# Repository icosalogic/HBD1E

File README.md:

# HBD1E
Kicad project for a configurable gate driver board to drive two MOSFETs with TO-247-4 package and
pinout [Drain, Source, KelvinSource, Gate].

Front side of board:

Back side of board:

# Features

- Supports 2 independent channels with 1 MOSFET per channel.
- No high-power connections on the board.  The user is free to connect the MOSFET power pins in any configuration they wish.
- Utilizes a gate driver chip in an SOIC-16 wide package, with a pin layout supported by multiple vendors.
- Each channel can be independently configured to be isolated from the gate driver control circuit.
- Each channel can be independently configured to use a linear regulator to precisely control the gate driver voltage.
- Most compatible gate driver chips support configurable dead time.

# Applications

- Half bridge, with input and output having a common ground: Configure the high side to be isolated, and the
low side non-isolated.
- T-Type inverter leg: Use 2 boards, with all gate power domains isolated, with the two middle MOSFETs configured
appropriately for common drain or common source.
- High power parallel MOSFETs: Disable dead time on the gate driver chip, and configure both MOSFET power
domains as non-isolated.

# Board Connections

Board input pins:  

- PWMH: PWM signal for the high-side MOSFET Q1, uses typical CMOS switching levels (off <= 0.8V, on >= 2.0V).
- PWML: PWM signal for the low-side MOSFET Q2, uses typical CMOS switching levels.
- DISABL: Pull this value low to enable the driver chip.  There is a pull up resistor to VCC on this circuit,
so the control component must pull this signal low to enable switching.  Uses typical CMOS switching levels.
- GND: Ground common to VCC and VGD.
- VCC: Power to the control side of the gate driver chip.  Typically 3.3V or 5V, maximum 20V.
- VGD: Power to the gate driver regions, optionally through isolation modules.

For the reference gate driver chip UCC21520, VCC and VGD may be the same for applications with lower
gate voltages.  Or you may choose to have them be separate, and use a higher voltage VGD to gain headroom
through the isolated modules, and configure the linear regulators to provide a precise post-isolation
gate drive voltage.

Note that there are no on-board connections for the high-current drain and source pins for either
MOSFET Q1 or Q2.  These must be connected separately, either through appropriately-sized wires or
a properly-designed laminated bus.

# Schematic

# PCB Layout Details

PCB components:

Front copper layer:

Back copper layer:

# Configuring Channel Isolation

The front of the board has marked locations for two DC-DC isolated modules, U3 (high side, shown below) and U5 (low side).

These modules take power from the VGD pin, and supply it to the regions of the PCB driving the gates for
the high side MOSFET Q1 and the low side MOSFET Q2.

To make either region isolated, solder a DC-DC isolated converter module in the marked location.
Our test boards used a Gaptec 3S7B-2424S3UP, but pin-compatible 7-SIP components are available from multiple manufacturers.

To make one of these power domains non-isolated, solder a wire connection from + to + and another from - to -.
Ordinary AWG 20 gauge hookup wire is adequate.

# Configuring Gate Drive Voltage Regulation

On the back side of the board, under the isolated modules U3 and U5, are locations for LM317 linear regulators
and associated components.

- High Side: (under U3) U4, D3, D4, C10, C11, R14, R15, R16
- Low Side: (under U5) U2, D1, D2, C7, C9, R11, R12, R13

The following table shows which resistors on this board map to those in a typical LM317 datasheet.
This should allow you to select resistor values to configure your desired gate driver voltage.

| Datasheet | High Side | Low Side |
| --------- | --------- | -------- |
|    R1     |    R16    |   R11    |
|    R2     |  R14+R15  | R12+R13  |

Note that we used 2 resistors in series for the R2 resistor from the datasheet.
The power dissipation from the minimum regulation current may exceed the limit for a typical
1/10 watt resistor, so we use 2 resistors in series to spread the thermal load.

Here is a table showing combinations for some typical gate drive voltages, using common resistor values.
Of course, more precise voltages can be obtained using more specific resistor values and higher
tolerance 0.1% resistors.

| Target Voltage | R16/R11 | R14+R15/R12+R13 | Computed Voltage |
| -------------- | ------- | --------------- | ---------------- |
|       10       |   180   |     270/1000    |      10.069      |
|       12       |   180   |     560/1000    |      12.083      |
|       15       |   180   |    1000/1000    |      15.139      |
|       18       |   180   |    1200/1200    |      17.917      |
|       20       |   180   |    1200/1500    |      20.000      |

Note also that the LM317 is a very robust device that may not require all the configured components.
The adjust capacitors may be omitted if your testing shows that ripple and other voltage transients
do not cause any downstream issues when switching the MOSFETs.
Each of the adjust capacitors is paired with a diode:

- C9, D2
- C11, D4

If you omit the adjust capacitor, you can also omit the matching diode.  If you use the adjust capacitor,
you should also use the diode to prevent the capacitor from discharging through the regulator in a power off
scenario.

Also note that you should always populate D1 and D3, since there are large capacitors for the gate driver
chip that may discharge through the regulator in a power off scenario.  D1 and D3 will prevent this.

To configure either the high-side or low-side power domain for voltage regulation, populate the associated
components as listed above.

To configure either of the power domains without voltage regulation, omit all of the regulation components
listed above for that domain, and replace the associated diode (D1 or D3) with a 0 ohm shunt resistor.

# Configuring Dead Time

The components used to configure dead time are R1, R10 and C6.

Some, but not all of the pin-compatible gate driver chips support controlling dead time between Q1 and Q2
gate transitions, using a resistor connected to pin 6.  If the gate driver chip you use does not support dead
time generation, then do not populate R1, R10 and C6, and ignore the rest of this section.

If your gate driver chip supports dead time insertion, populate R10 and optionally C6 according to the
datasheet for your chip.  Do not populate R1.

If your chip supports dead time insertion, but you wish to suppress it, populate R1, but not R10 and C6.
This may be desireable if you use this board in a high-current parallel MOSFET application, where you want
both MOSFETs on at the same time.

If your control logic providing the PWM signals also implements dead time, one strategy is to program an
absolute minimum dead time via the hardware as described in this section, and program an optimized, longer
dead time in your control logic.  The gate driver chip uses the longer of the hardware configured dead
time or the software-controlled dead time in the PWM inputs.

# Configuring Input Signal Filtering

Each of the 3 input signals from the controller to this gate driver board has an RC circuit to
filter transients that may cause issues for the gate driver IC input logic.  These signals and the
associated filter components are listed below.

| Signal Name | Filter Resistor | Value | Capacitor | Value | Pull Up Resistor | Value |
| ----------- | --------------- | ----- | --------- | ----- | ---------------- | ----- |
|     PWMH    |       R4        |  47Ω   |     C1    |  33pF |                  |       |
|     PWML    |       R5        |  47Ω   |     C4    |  33pF |                  |       |
|    DISABL   |       R6        |  47Ω   |     C5    |   1nF |        R7        |  10k  |

The size of all these components is 0805, making them less trouble to hand solder while changing
filter components.

# Test Points

There are numerous test points located on both sides of the board to which users can solder
surface mount test point loops, for example KOA Speer RCWCTE.
This gives you the ability to clip oscilloscope leads to enable monitoring various signals while
debugging the gate driver configuration.

### Caution!  This board may use high voltages that are hazardous to humans.
- Be very careful when connecting test leads to potentially high voltage points on the circuit board.
- High voltages may also break test equipment if proper grounding and isolation practices are not followed.
- Please be careful!

List of test points on the board:
| Label |  Name    | Location | Description                                     |
| ----- | ------   | -------- | ----------------------------------------------- |
| TP1   | HS Gate  | Bottom   | High side MOSFET gate pin                       |
| TP2   | LS Gate  | Bottom   | Low side MOSFET gate pin                        |
| TP3   | VDDB     | Bottom   | Low side post-regulated gate driver voltage     |
| TP4   | VDDA     | Top      | High side post-regulated gate driver voltage    |
| TP5   | VDDA_ISO | Bottom   | High side post-isolation, pre-regulated voltage |
| TP6   | PWMHF    | Top      | High side post-filter PWM input signal          |
| TP7   | PWMLF    | Top      | Low side post-filter PWM input signal           |
| TP8   | DISF     | Top      | Disable post-filter input signal                |
| TP9   | VCC      | Top      | Logic side power for gate driver chip           |
| TP10  | VGD      | Bottom   | Pre-isolation gate driver voltage               |
| TP11  | VDDB_ISO | Bottom   | Low side post-isolation, pre-regulated voltage  |

# Reference Components

- Gate driver chip: Texas Instruments UCC21520
- MOSFET: Infineon AIMZH120R020M1TXKSA1
- Isolated DC-DC module: Gaptec 3S7B-2424S3UP
- Linear Regulator: Texas Instruments LM317

# Example Bill of Materials (BOM)

An example BOM is located in the file HBD1E_BOM.csv.

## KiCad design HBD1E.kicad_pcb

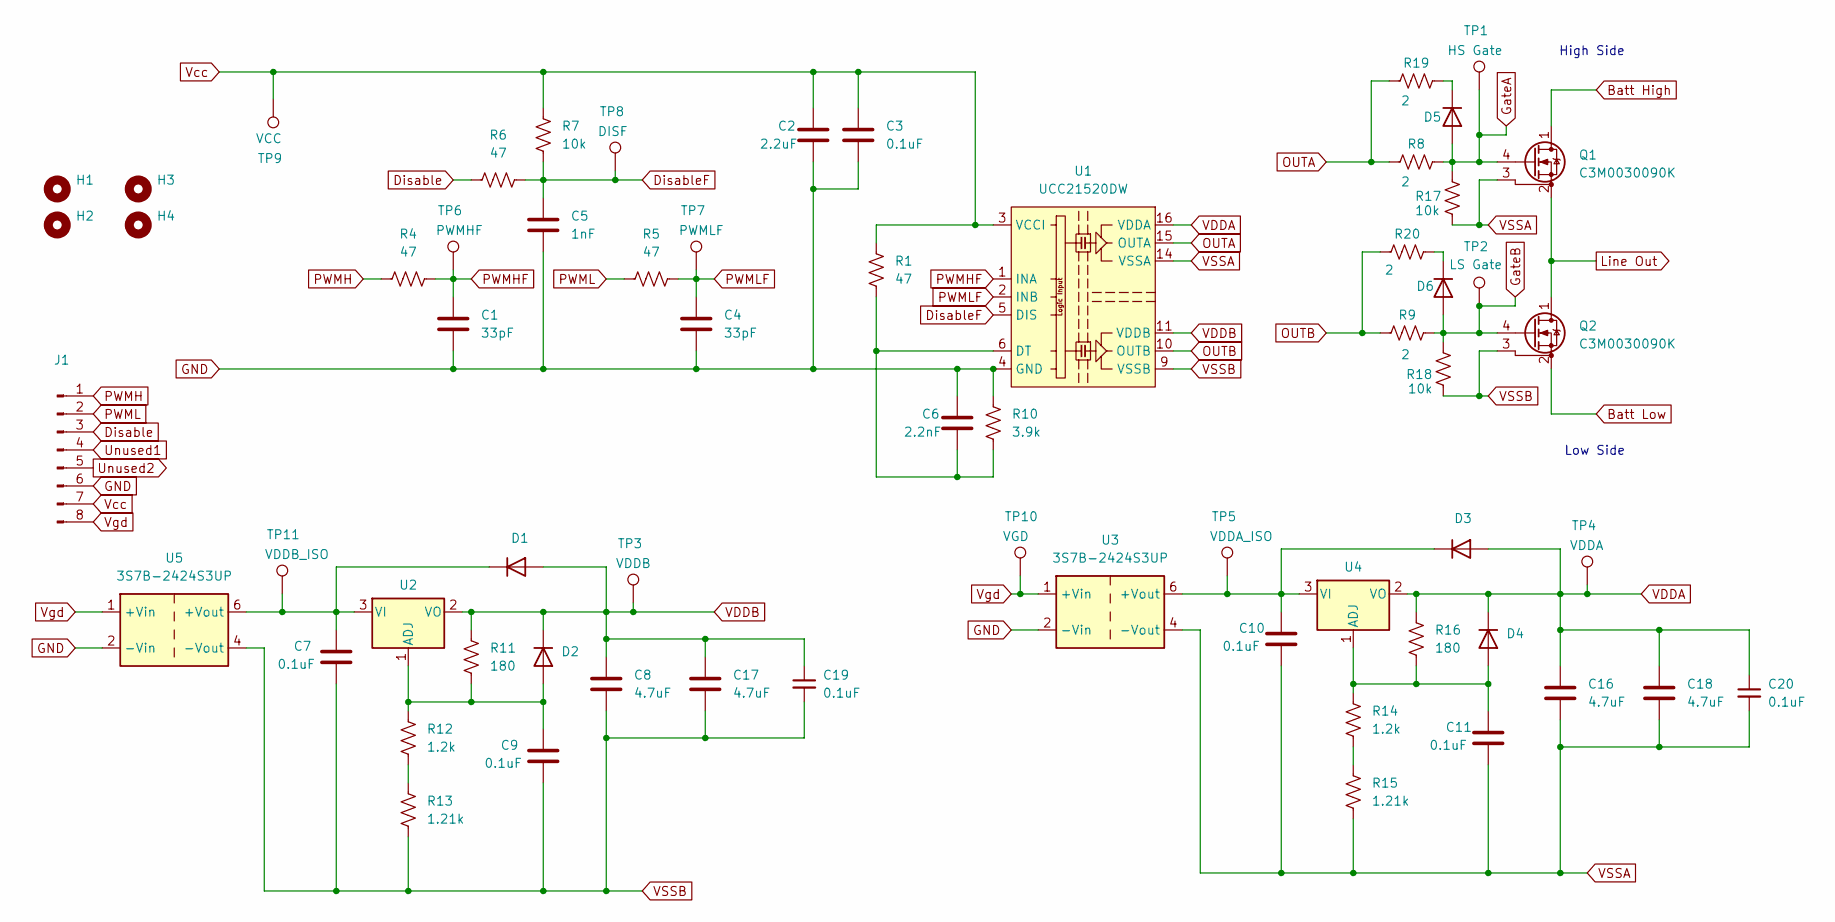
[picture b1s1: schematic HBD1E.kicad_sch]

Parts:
C1, C4: 33pF; C_0805_2012Metric_Pad1.18x1.45mm_HandSolder
C2: 2.2uF; CP_EIA-6032-20_AVX-F_Pad2.25x2.35mm_HandSolder
C3, C7, C9, C10, C11, C19, C20: 0.1uF; C_0805_2012Metric_Pad1.18x1.45mm_HandSolder
C5: 1nF; C_0805_2012Metric_Pad1.18x1.45mm_HandSolder
C6: 2.2nF; C_0805_2012Metric
C8, C16, C17, C18: 4.7uF; C_1210_3225Metric
D1, D2, D3, D4: US1B; D_0805_2012Metric_Pad1.15x1.40mm_HandSolder
D5, D6: US1B; D_SMA
H1, H2: MountingHole; MountingHole_2.7mm_M2.5_Pad_TopBottom
H3, H4: MountingHole; MountingHole_2.7mm
J1: Conn_01x08_Male; PinHeader_1x08_P2.54mm_Vertical
Q1, Q2: C3M0030090K; TO-247-4_Vertical
R1, R4, R5, R6: 47; R_0805_2012Metric_Pad1.20x1.40mm_HandSolder
R7, R17, R18: 10k; R_0805_2012Metric_Pad1.20x1.40mm_HandSolder
R8, R9, R19, R20: 2; R_2512_6332Metric_Pad1.40x3.35mm_HandSolder
R10: 3.9k; R_0805_2012Metric_Pad1.20x1.40mm_HandSolder
R11, R16: 180; R_0805_2012Metric_Pad1.20x1.40mm_HandSolder
R12, R14: 1.2k; R_0805_2012Metric_Pad1.20x1.40mm_HandSolder
R13, R15: 1.21k; R_0805_2012Metric_Pad1.20x1.40mm_HandSolder
TP1: HS Gate; TestPoint_Pad_4.0x4.0mm
TP2: LS Gate; TestPoint_Pad_4.0x4.0mm
TP3: VDDB; TestPoint_Pad_4.0x4.0mm
TP4: VDDA; TestPoint_Pad_4.0x4.0mm
TP5: VDDA_ISO; TestPoint_Pad_4.0x4.0mm
TP6: PWMHF; TestPoint_Pad_4.0x4.0mm
TP7: PWMLF; TestPoint_Pad_4.0x4.0mm
TP8: DISF; TestPoint_Pad_4.0x4.0mm
TP9: VCC; TestPoint_Pad_4.0x4.0mm
TP10: VGD; TestPoint_Pad_4.0x4.0mm
TP11: VDDB_ISO; TestPoint_Pad_4.0x4.0mm
U1: UCC21520DW; SOIC-16W_7.5x10.3mm_P1.27mm_no_pins_12_13
U2, U4: LM317_SOT-223; SOT-223-3_TabPin2
U3, U5: 3S7B-2424S3UP; Converter_DCDC_TRACO_TBA2-xxxx_Single_THT

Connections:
Batt High: Q1.1 (D)
Batt Low: Q2.2 (S)
Disable: J1.3, R6.2
DisableF: C5.1, R6.1, R7.1, TP8.1, U1.5 (DIS)
GND: C1.2, C2.2, C3.2, C4.2, C5.2, C6.1, J1.6, R10.2, U1.4 (GND), U3.2 (-Vin), U5.2 (-Vin)
GateA: D5.2 (A), Q1.4 (G), R8.1, R17.2, TP1.1
GateB: D6.2 (A), Q2.4 (G), R9.1, R18.2, TP2.1
Line Out: Q1.2 (S), Q2.1 (D)
unnamed: C7.1, D1.1 (K), TP11.1, U2.3 (VI), U5.6 (+Vout)
unnamed: C9.1, D2.2 (A), R11.1, R12.2, U2.1 (ADJ)
unnamed: C10.1, D3.1 (K), TP5.1, U3.6 (+Vout), U4.3 (VI)
unnamed: C11.1, D4.2 (A), R14.2, R16.1, U4.1 (ADJ)
unnamed: D5.1 (K), R19.1
unnamed: D6.1 (K), R20.1
unnamed: R12.1, R13.2
unnamed: R14.1, R15.2
unnamed: C6.2, R1.1, R10.1, U1.6 (DT)
OUTA: R8.2, R19.2, U1.15 (OUTA)
OUTB: R9.2, R20.2, U1.10 (OUTB)
PWMH: J1.1, R4.2
PWMHF: C1.1, R4.1, TP6.1, U1.1 (INA)
PWML: J1.2, R5.2
PWMLF: C4.1, R5.1, TP7.1, U1.2 (INB)
Unused1: J1.4
Unused2: J1.5
VDDA: C16.1, C18.1, C20.1, D3.2 (A), D4.1 (K), R16.2, TP4.1, U1.16 (VDDA), U4.2 (VO)
VDDB: C8.1, C17.1, C19.1, D1.2 (A), D2.1 (K), R11.2, TP3.1, U1.11 (VDDB), U2.2 (VO)
VSSA: C10.2, C11.2, C16.2, C18.2, C20.2, Q1.3 (DS), R15.1, R17.1, U1.14 (VSSA), U3.4 (-Vout)
VSSB: C7.2, C8.2, C9.2, C17.2, C19.2, Q2.3 (DS), R13.1, R18.1, U1.9 (VSSB), U5.4 (-Vout)
Vcc: C2.1, C3.1, J1.7, R1.2, R7.2, TP9.1, U1.3 (VCCI), U1.8 (VCCI)
Vgd: J1.8, TP10.1, U3.1 (+Vin), U5.1 (+Vin)

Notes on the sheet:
High Side
Low Side

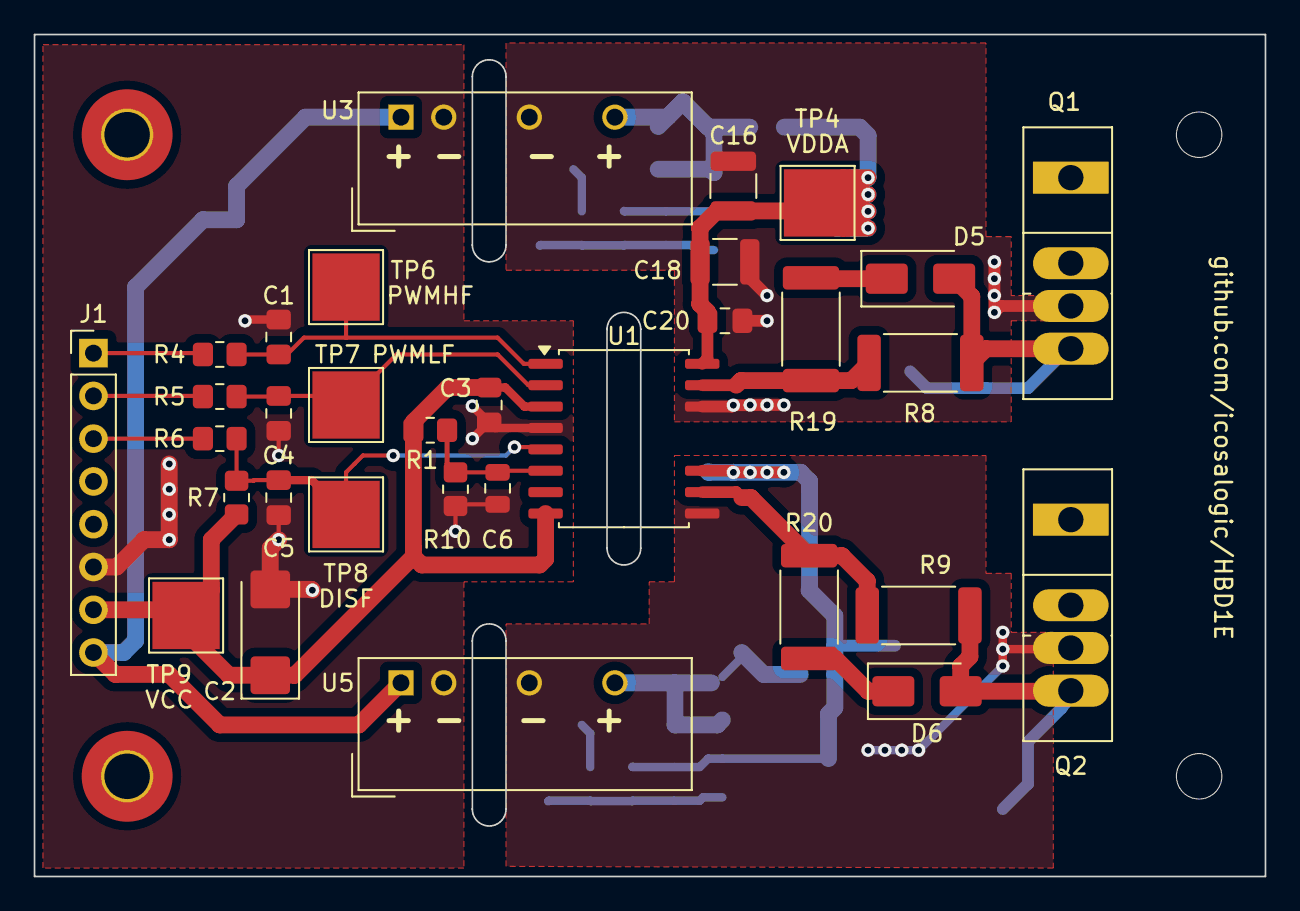
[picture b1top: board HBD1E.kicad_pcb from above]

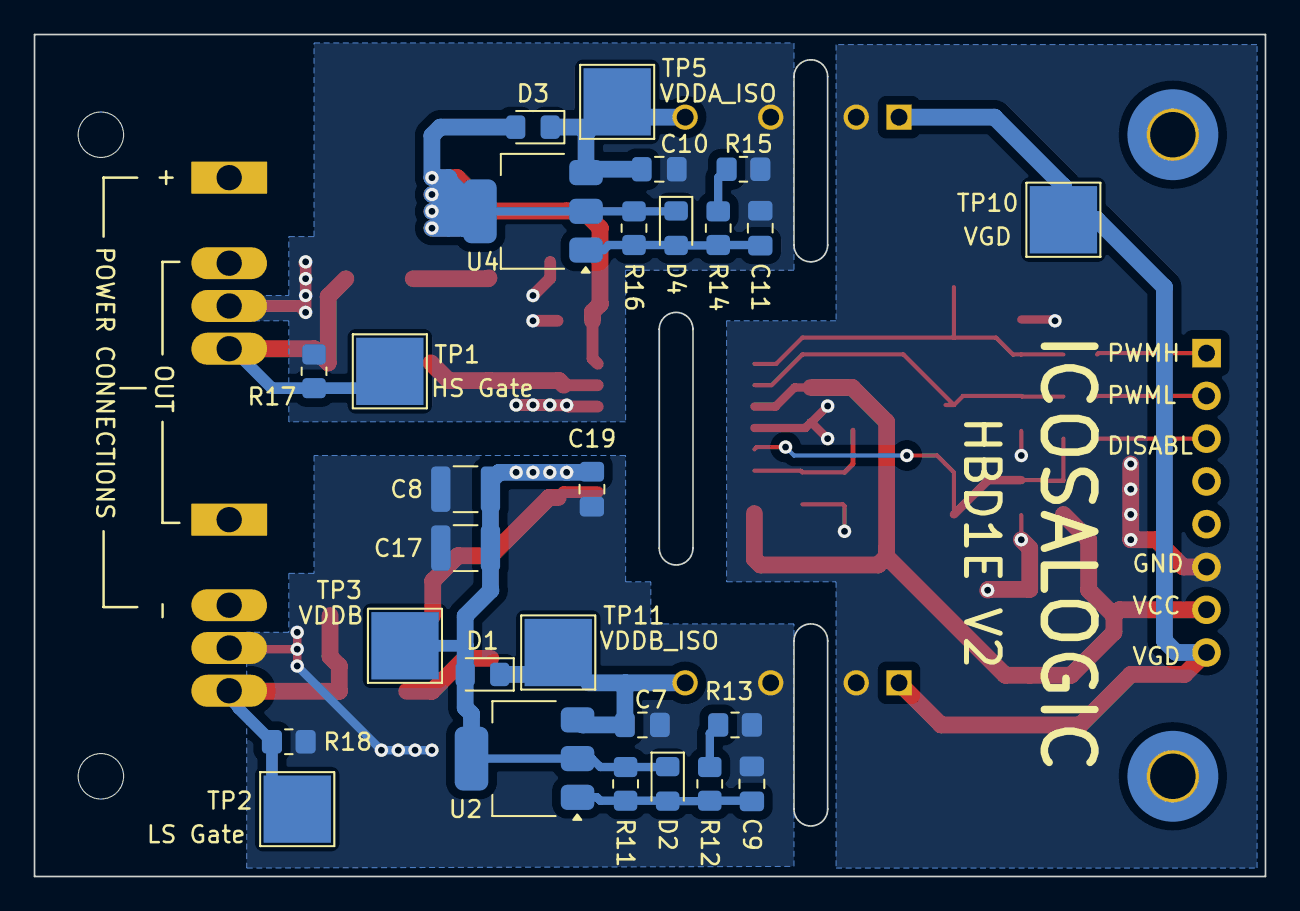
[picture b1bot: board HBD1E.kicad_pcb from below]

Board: 2 copper layers, 73.1 x 50.0 mm, 63 parts (27 on the bottom side), 27 nets.

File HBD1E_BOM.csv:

"Id";"Designator";"Footprint";"Quantity";"Designation";"Supplier and ref";
1;"TP4";"TestPoint_Pad_4.0x4.0mm";1;"VDDA";;;
2;"H2,H1";"MountingHole_2.7mm_M2.5_Pad_TopBottom";2;"MountingHole";;;
3;"Q1,Q2";"TO-247-4_Vertical";2;"C3M0030090K";;;
4;"C5";"C_0805_2012Metric_Pad1.18x1.45mm_HandSolder";1;"1nF";;;
5;"C2";"CP_EIA-6032-20_AVX-F_Pad2.25x2.35mm_HandSolder";1;"2.2uF";;;
6;"R6,R5,R1,R4";"R_0805_2012Metric_Pad1.20x1.40mm_HandSolder";4;"47";;;
7;"D5,D6";"D_SMA";2;"US1B";;;
8;"TP9";"TestPoint_Pad_4.0x4.0mm";1;"VCC";;;
9;"TP6";"TestPoint_Pad_4.0x4.0mm";1;"PWMHF";;;
10;"R9,R19,R20,R8";"R_2512_6332Metric_Pad1.40x3.35mm_HandSolder";4;"2";;;
11;"TP7";"TestPoint_Pad_4.0x4.0mm";1;"PWMLF";;;
12;"C1,C4";"C_0805_2012Metric_Pad1.18x1.45mm_HandSolder";2;"33pF";;;
13;"C6";"C_0805_2012Metric";1;"2.2nF";;;
14;"U5,U3";"Converter_DCDC_TRACO_TBA2-xxxx_Single_THT";2;"3S7B-2424S3UP";;;
15;"R10";"R_0805_2012Metric_Pad1.20x1.40mm_HandSolder";1;"3.9k";;;
16;"C3,C20,C9,C10,C7,C19,C11";"C_0805_2012Metric_Pad1.18x1.45mm_HandSolder";7;"0.1uF";;;
17;"C16,C18,C17,C8";"C_1210_3225Metric";4;"4.7uF";;;
18;"H4,H3";"MountingHole_2.7mm";2;"MountingHole";;;
19;"J1";"PinHeader_1x08_P2.54mm_Vertical";1;"Conn_01x08_Male";;;
20;"U1";"SOIC-16W_7.5x10.3mm_P1.27mm_no_pins_12_13";1;"UCC21520DW";;;
21;"R7,R17,R18";"R_0805_2012Metric_Pad1.20x1.40mm_HandSolder";3;"10k";;;
22;"TP8";"TestPoint_Pad_4.0x4.0mm";1;"DISF";;;
23;"TP2";"TestPoint_Pad_4.0x4.0mm";1;"LS Gate";;;
24;"TP1";"TestPoint_Pad_4.0x4.0mm";1;"HS Gate";;;
25;"R11,R16";"R_0805_2012Metric_Pad1.20x1.40mm_HandSolder";2;"180";;;
26;"R14,R12";"R_0805_2012Metric_Pad1.20x1.40mm_HandSolder";2;"1.2k";;;
27;"R13,R15";"R_0805_2012Metric_Pad1.20x1.40mm_HandSolder";2;"1.21k";;;
28;"U2,U4";"SOT-223-3_TabPin2";2;"LM317_SOT-223";;;
29;"D4,D1,D3,D2";"D_0805_2012Metric_Pad1.15x1.40mm_HandSolder";4;"US1B";;;
30;"TP10";"TestPoint_Pad_4.0x4.0mm";1;"VGD";;;
31;"TP5";"TestPoint_Pad_4.0x4.0mm";1;"VDDA_ISO";;;
32;"TP3";"TestPoint_Pad_4.0x4.0mm";1;"VDDB";;;
33;"TP11";"TestPoint_Pad_4.0x4.0mm";1;"VDDB_ISO";;;

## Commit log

2025-04-02 Initial checkin.
2025-04-02 Initial checkin of gerber files.
2025-04-03 First check in of board image files.
2025-04-03 First version of real README contents.
2025-04-03 Added more detail to the README file.
2025-04-03 Added a pull-up resistor for dead time configuration.
2025-04-03 Updated dead time configuration section of README file.
2025-04-03 Added a table to README describing which resistors determine linear regulator output voltage.
2025-04-03 Fixed incorrect project location in PCB text object.
2025-04-26 Updated README for input filters and test points. Changed name in license file.
2025-04-26 Two small README tweaks.
2025-04-28 Added a BOM file and updated README with possible LM317 resistor combinations for typical gate drive voltages.
